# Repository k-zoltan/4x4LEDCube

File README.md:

# 4x4LEDCube
4x4 LED cube with blue LEDs and Atmega16

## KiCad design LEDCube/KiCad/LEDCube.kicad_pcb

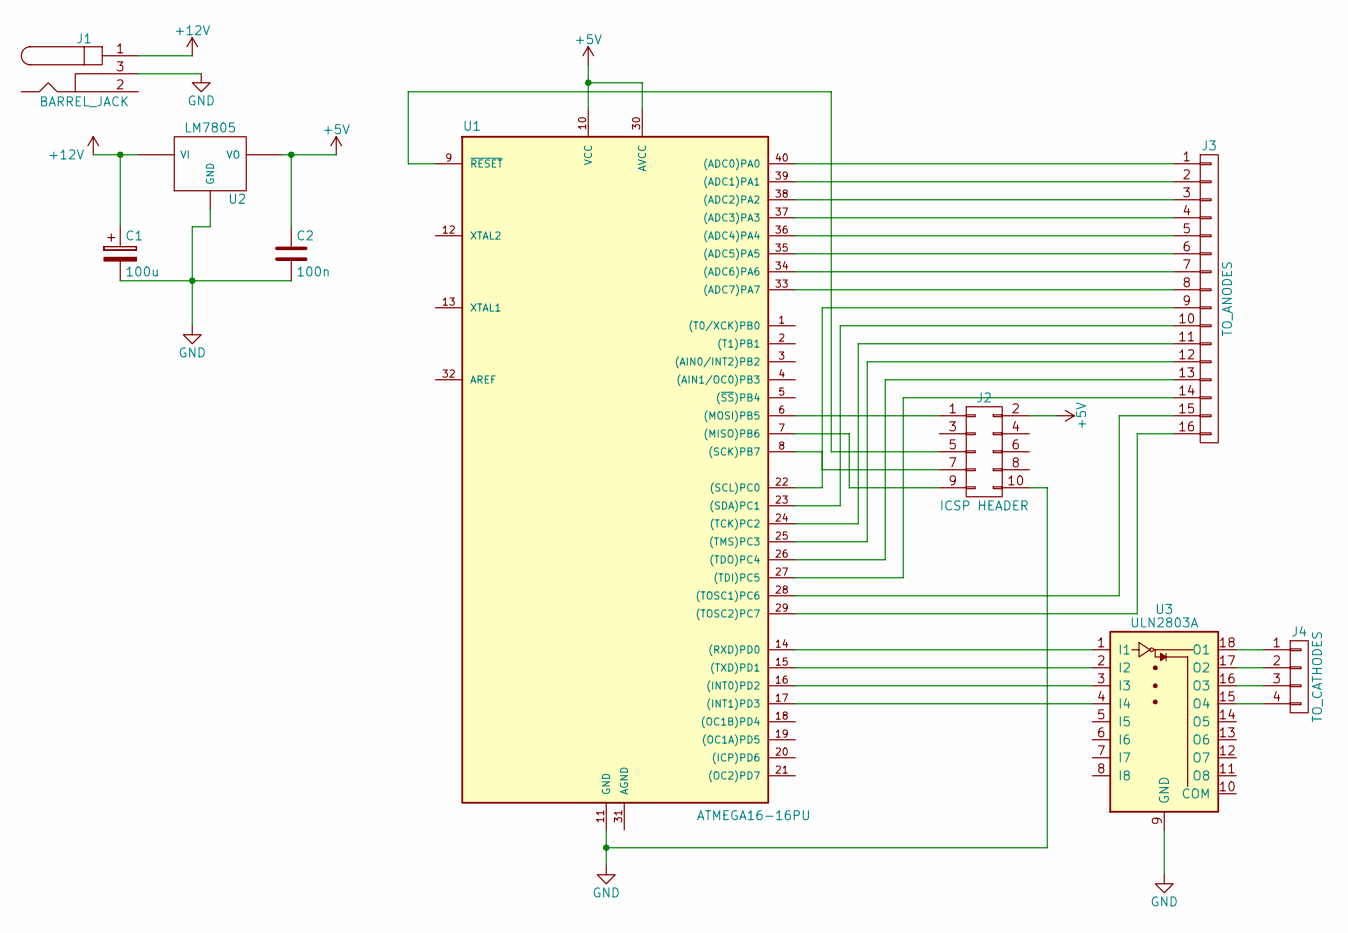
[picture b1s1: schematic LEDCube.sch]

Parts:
C1: 100u; CP_Elec_6.3x7.7
C2: 100n; C_1206_HandSoldering
J1: BARREL_JACK
J2: ICSP HEADER; Pin_Header_Straight_2x05_Pitch2.54mm
J3: TO_ANODES; Pin_Header_Straight_1x16_Pitch2.54mm
J4: TO_CATHODES; Pin_Header_Straight_1x04_Pitch2.54mm
U1: ATMEGA16-16PU; DIP-40_W15.24mm_Socket_LongPads
U2: LM7805; TO-220-3_Horizontal
U3: ULN2803A; DIP-18_W7.62mm_Socket_LongPads

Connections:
+5V: C2.1, J2.2, U1.10 (VCC), U1.30 (AVCC), U2.3 (VO)
+12V: C1.1, J1.1, U2.1 (VI)
GND: C1.2, C2.2, J1.3, J2.10, U1.11 (GND), U2.2 (GND), U3.9 (GND)
unnamed: J2.1, U1.6 ((MOSI)PB5)
unnamed: J2.5, U1.9 (~RESET)
unnamed: J2.7, U1.8 ((SCK)PB7)
unnamed: J2.9, U1.7 ((MISO)PB6)
unnamed: J3.1, U1.40 ((ADC0)PA0)
unnamed: J3.2, U1.39 ((ADC1)PA1)
unnamed: J3.3, U1.38 ((ADC2)PA2)
unnamed: J3.4, U1.37 ((ADC3)PA3)
unnamed: J3.5, U1.36 ((ADC4)PA4)
unnamed: J3.6, U1.35 ((ADC5)PA5)
unnamed: J3.7, U1.34 ((ADC6)PA6)
unnamed: J3.8, U1.33 ((ADC7)PA7)
unnamed: J3.9, U1.22 ((SCL)PC0)
unnamed: J3.10, U1.23 ((SDA)PC1)
unnamed: J3.11, U1.24 ((TCK)PC2)
unnamed: J3.12, U1.25 ((TMS)PC3)
unnamed: J3.13, U1.26 ((TDO)PC4)
unnamed: J3.14, U1.27 ((TDI)PC5)
unnamed: J3.15, U1.28 ((TOSC1)PC6)
unnamed: J3.16, U1.29 ((TOSC2)PC7)
unnamed: J4.1, U3.18 (O1)
unnamed: J4.2, U3.17 (O2)
unnamed: J4.3, U3.16 (O3)
unnamed: J4.4, U3.15 (O4)
unnamed: U1.14 ((RXD)PD0), U3.1 (I1)
unnamed: U1.15 ((TXD)PD1), U3.2 (I2)
unnamed: U1.16 ((INT0)PD2), U3.3 (I3)
unnamed: U1.17 ((INT1)PD3), U3.4 (I4)

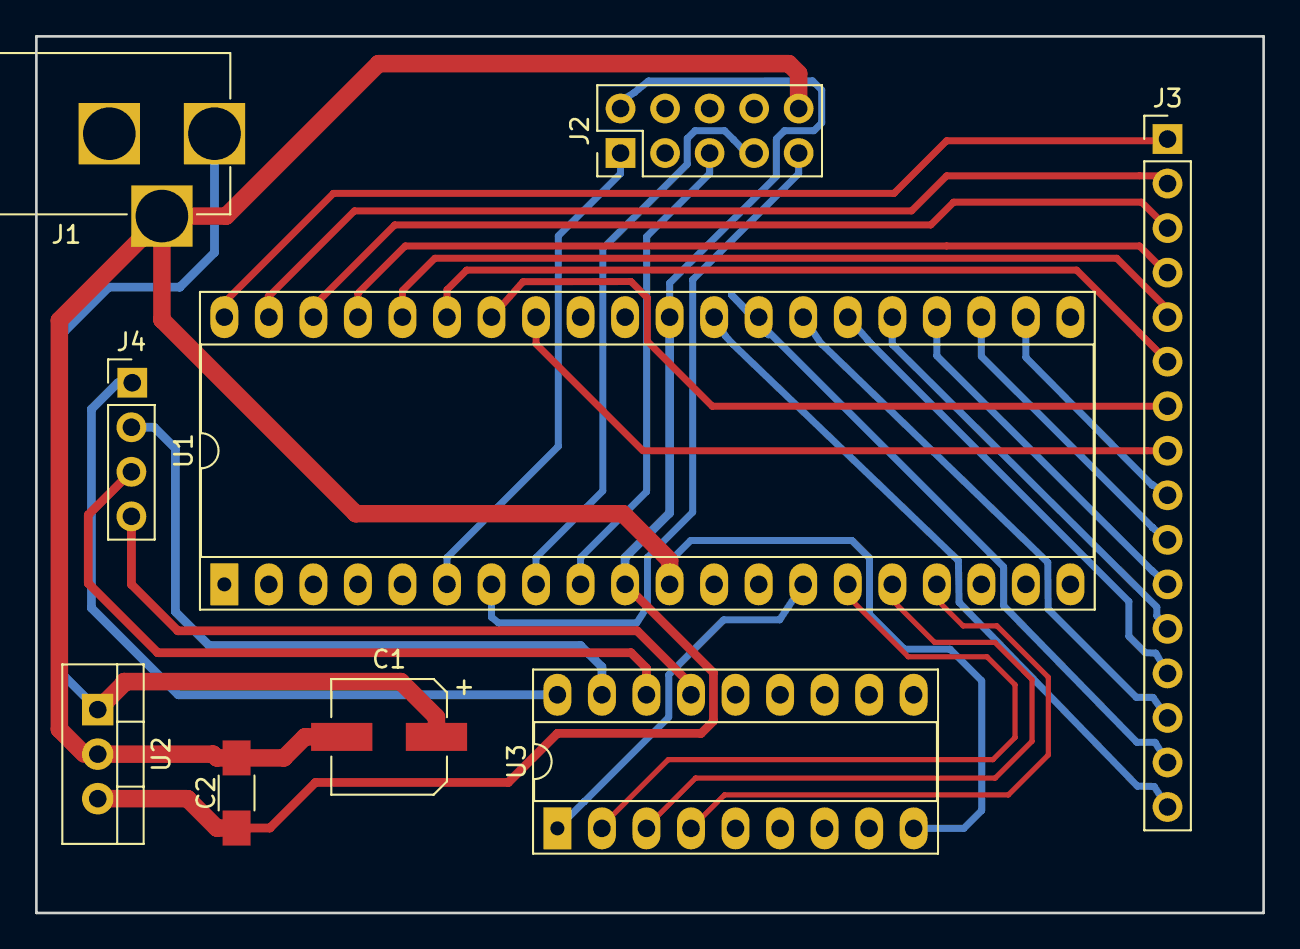
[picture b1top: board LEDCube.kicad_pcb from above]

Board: 2 copper layers, 70.0 x 50.0 mm, 9 parts (0 on the bottom side), 31 nets.

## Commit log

2018-01-08 Tracks changed
    Tracks and track widths changed.
2018-01-09 Minor changes
2018-02-06 AVR program changed
